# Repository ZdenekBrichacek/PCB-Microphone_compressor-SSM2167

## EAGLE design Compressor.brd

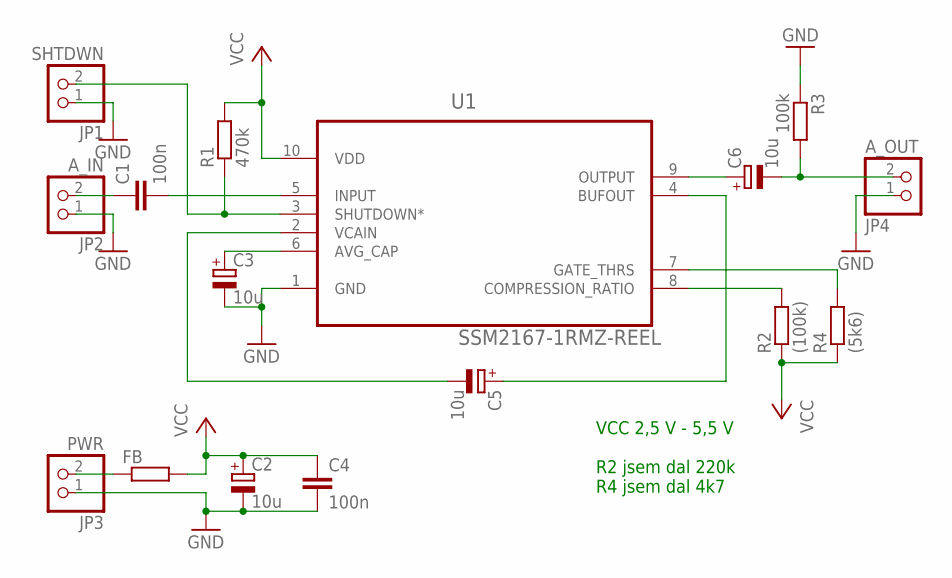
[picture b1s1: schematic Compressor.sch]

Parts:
C1, C4: 100n; C0603
C2, C3, C5, C6: 10u; SMC_A
FB: R-EU_R0603; R0603
JP1: SHTDWN; 1X02
JP2: A_IN; 1X02
JP3: PWR; 1X02
JP4: A_OUT; 1X02
R1: 470k; R0603
R2: (100k); R0603
R3: 100k; R0603
R4: (5k6); R0603
U1: SSM2167-1RMZ-REEL; SOP50P490X110-10N

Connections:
GND: C2.-, C3.-, C4.2, JP1.1, JP2.1, JP3.1, JP4.1, R3.1, U1.1 (GND)
unnamed: C1.1, JP2.2
unnamed: C1.2, U1.5 (INPUT)
unnamed: C5.-, U1.2 (VCAIN)
unnamed: C5.+, U1.4 (BUFOUT)
unnamed: C3.+, U1.6 (AVG_CAP)
unnamed: JP1.2, R1.1, U1.3 (SHUTDOWN*)
unnamed: R2.2, U1.8 (COMPRESSION_RATIO)
unnamed: R4.2, U1.7 (GATE_THRS)
unnamed: C6.+, U1.9 (OUTPUT)
unnamed: C6.-, JP4.2, R3.2
unnamed: FB.1, JP3.2
VCC: C2.+, C4.1, FB.2, R1.2, R2.1, R4.1, U1.10 (VDD)

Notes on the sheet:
VCC 2,5 V - 5,5 V R2 jsem dal 220k R4 jsem dal 4k7

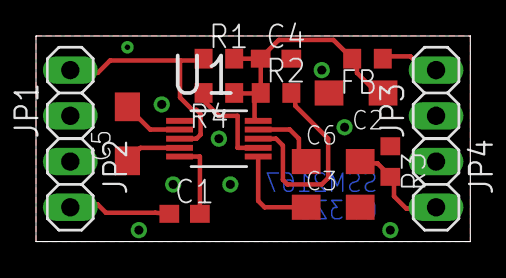
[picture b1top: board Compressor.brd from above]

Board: 2 copper layers, 24.1 x 11.4 mm, 16 parts (0 on the bottom side), 13 nets.

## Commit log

2017-10-10 :confetti_ball: Added .gitattributes & .gitignore files
2017-10-10 Initial version
